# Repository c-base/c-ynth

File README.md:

c-ynth
======

data collection and source files for synth

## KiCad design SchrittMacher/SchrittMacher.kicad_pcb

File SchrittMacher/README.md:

# SchrittMacher

## Features

* 16 Step sequencer
* Gate Out
* Clock Out
* Clock In
* Global CV Out
* CV Out per Step
* Reset Per Step
* Reset In 

## Parts

* 2x 4017

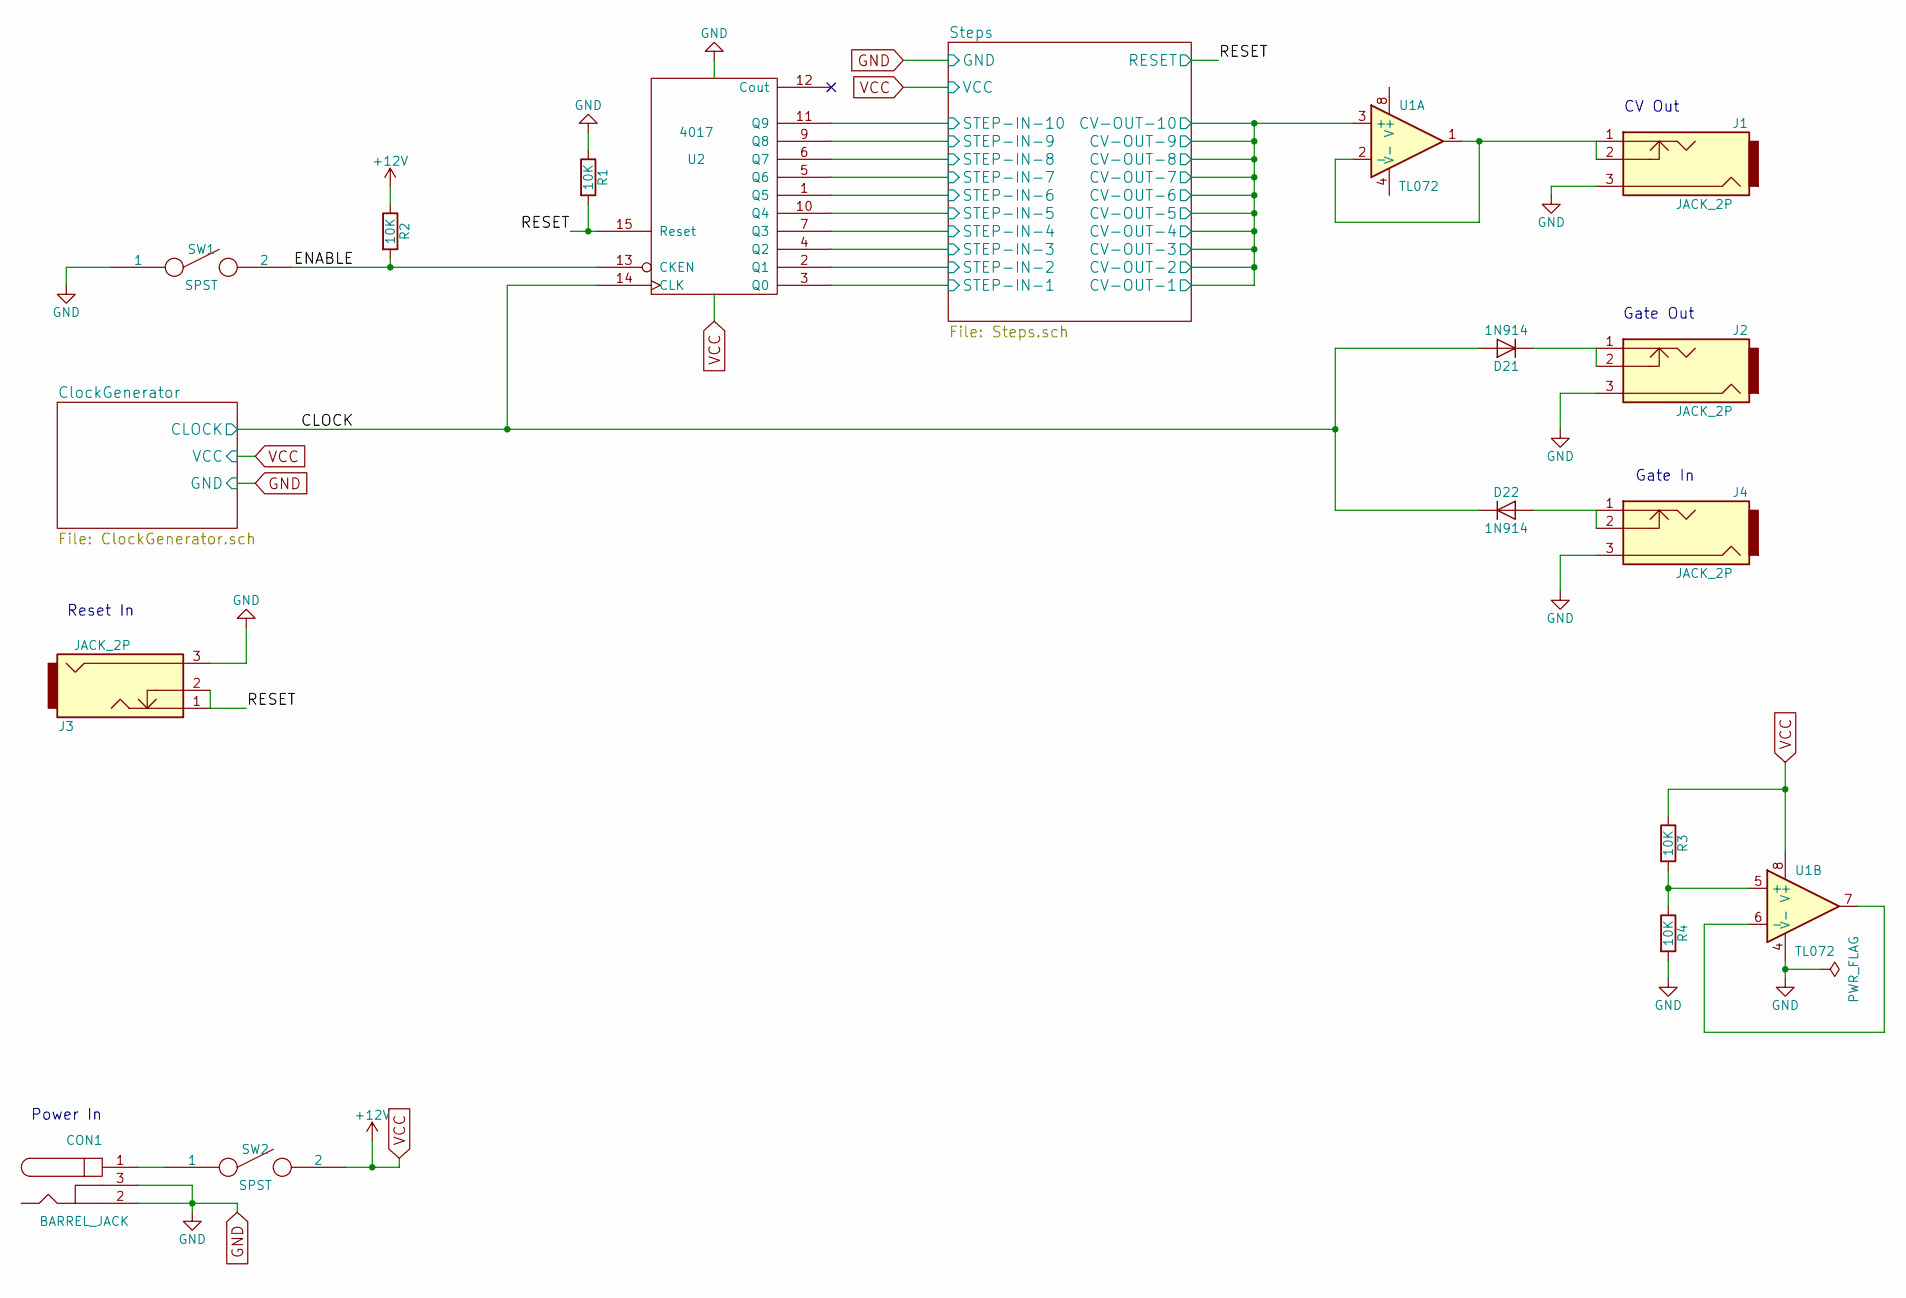
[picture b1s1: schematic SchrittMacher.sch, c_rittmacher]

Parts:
CON1: BARREL_JACK; JACK_ALIM
D21, D22: 1N914; Diode_DO-35_SOD27_Horizontal_RM10
J1, J2, J3, J4: JACK_2P; Socket_Strip_Straight_1x03
R1, R2, R3, R4: 10K; Resistor_Horizontal_RM10mm
SW1, SW2: SPST; Socket_Strip_Straight_1x02
U1: TL072; DIP-8_W7.62mm_LongPads
U2: 4017; DIP-16_W7.62mm_LongPads

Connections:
/CLOCK: D21.2 (A), D22.1 (K), U2.14 (CLK); also elsewhere on the board
/ENABLE: R2.2, SW1.2, U2.13 (CKEN)
/RESET: J3.1, J3.2, R1.2, U2.15 (Reset); also elsewhere on the board
/Steps/CV-OUT-1: U1.3 (+); also elsewhere on the board
/Steps/STEP-IN-1: U2.3 (Q0); also elsewhere on the board
/Steps/STEP-IN-2: U2.2 (Q1); also elsewhere on the board
/Steps/STEP-IN-3: U2.4 (Q2); also elsewhere on the board
/Steps/STEP-IN-4: U2.7 (Q3); also elsewhere on the board
/Steps/STEP-IN-5: U2.10 (Q4); also elsewhere on the board
/Steps/STEP-IN-6: U2.1 (Q5); also elsewhere on the board
/Steps/STEP-IN-7: U2.5 (Q6); also elsewhere on the board
/Steps/STEP-IN-8: U2.6 (Q7); also elsewhere on the board
/Steps/STEP-IN-9: U2.9 (Q8); also elsewhere on the board
/Steps/STEP-IN-10: U2.11 (Q9); also elsewhere on the board
GND: CON1.2, CON1.3, J1.3, J2.3, J3.3, J4.3, R1.1, R4.2, SW1.1, U1.4 (V-), U2.8 (VSS); also elsewhere on the board
unnamed: CON1.1, SW2.1
unnamed: D21.1 (K), J2.1, J2.2
unnamed: D22.2 (A), J4.1, J4.2
unnamed: J1.1, J1.2, U1.1, U1.2 (-)
unnamed: R3.2, R4.1, U1.5 (+)
unnamed: U1.6 (-), U1.7
VCC: R2.1, R3.1, SW2.2, U1.8 (V+), U2.16 (VDD); also elsewhere on the board

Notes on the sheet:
Gate Out
Reset In
Power In
CV Out
Gate In

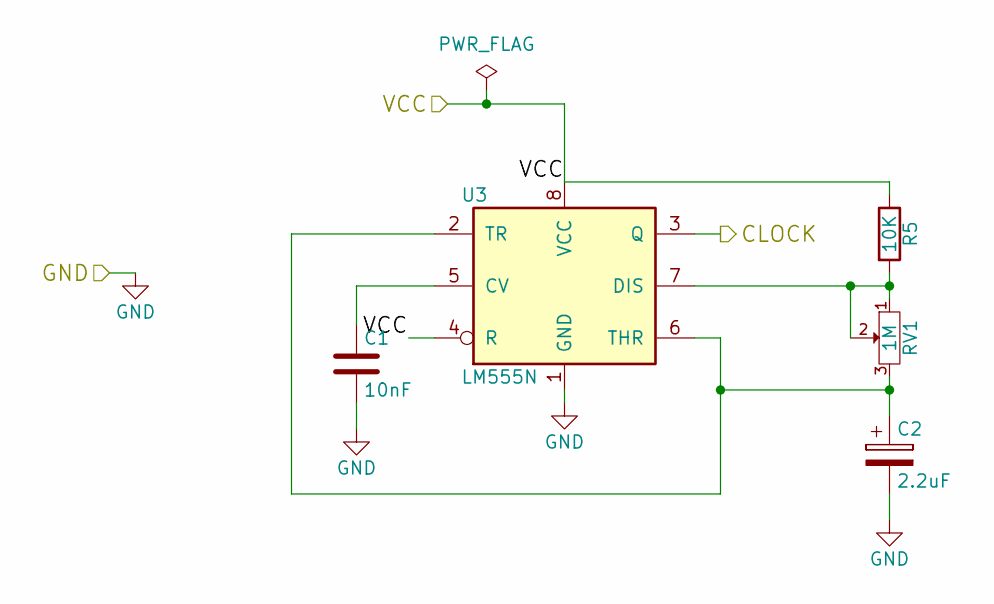
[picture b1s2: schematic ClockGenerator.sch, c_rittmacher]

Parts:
C1: 10nF; C_Disc_D3_P2.5
C2: 2.2uF; C_Radial_D5_L6_P2.5
R5: 10K; Resistor_Horizontal_RM10mm
RV1: 1M; Potentiometer_WirePads_Small
U3: LM555N; DIP-8_W7.62mm_LongPads

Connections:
/CLOCK: U3.3 (Q); also elsewhere on the board
GND: C1.2, C2.2, U3.1 (GND); also elsewhere on the board
unnamed: C1.1, U3.5 (CV)
unnamed: C2.1, RV1.3, U3.2 (TR), U3.6 (THR)
unnamed: R5.2, RV1.1, RV1.2, U3.7 (DIS)
VCC: R5.1, U3.4 (R), U3.8 (VCC); also elsewhere on the board

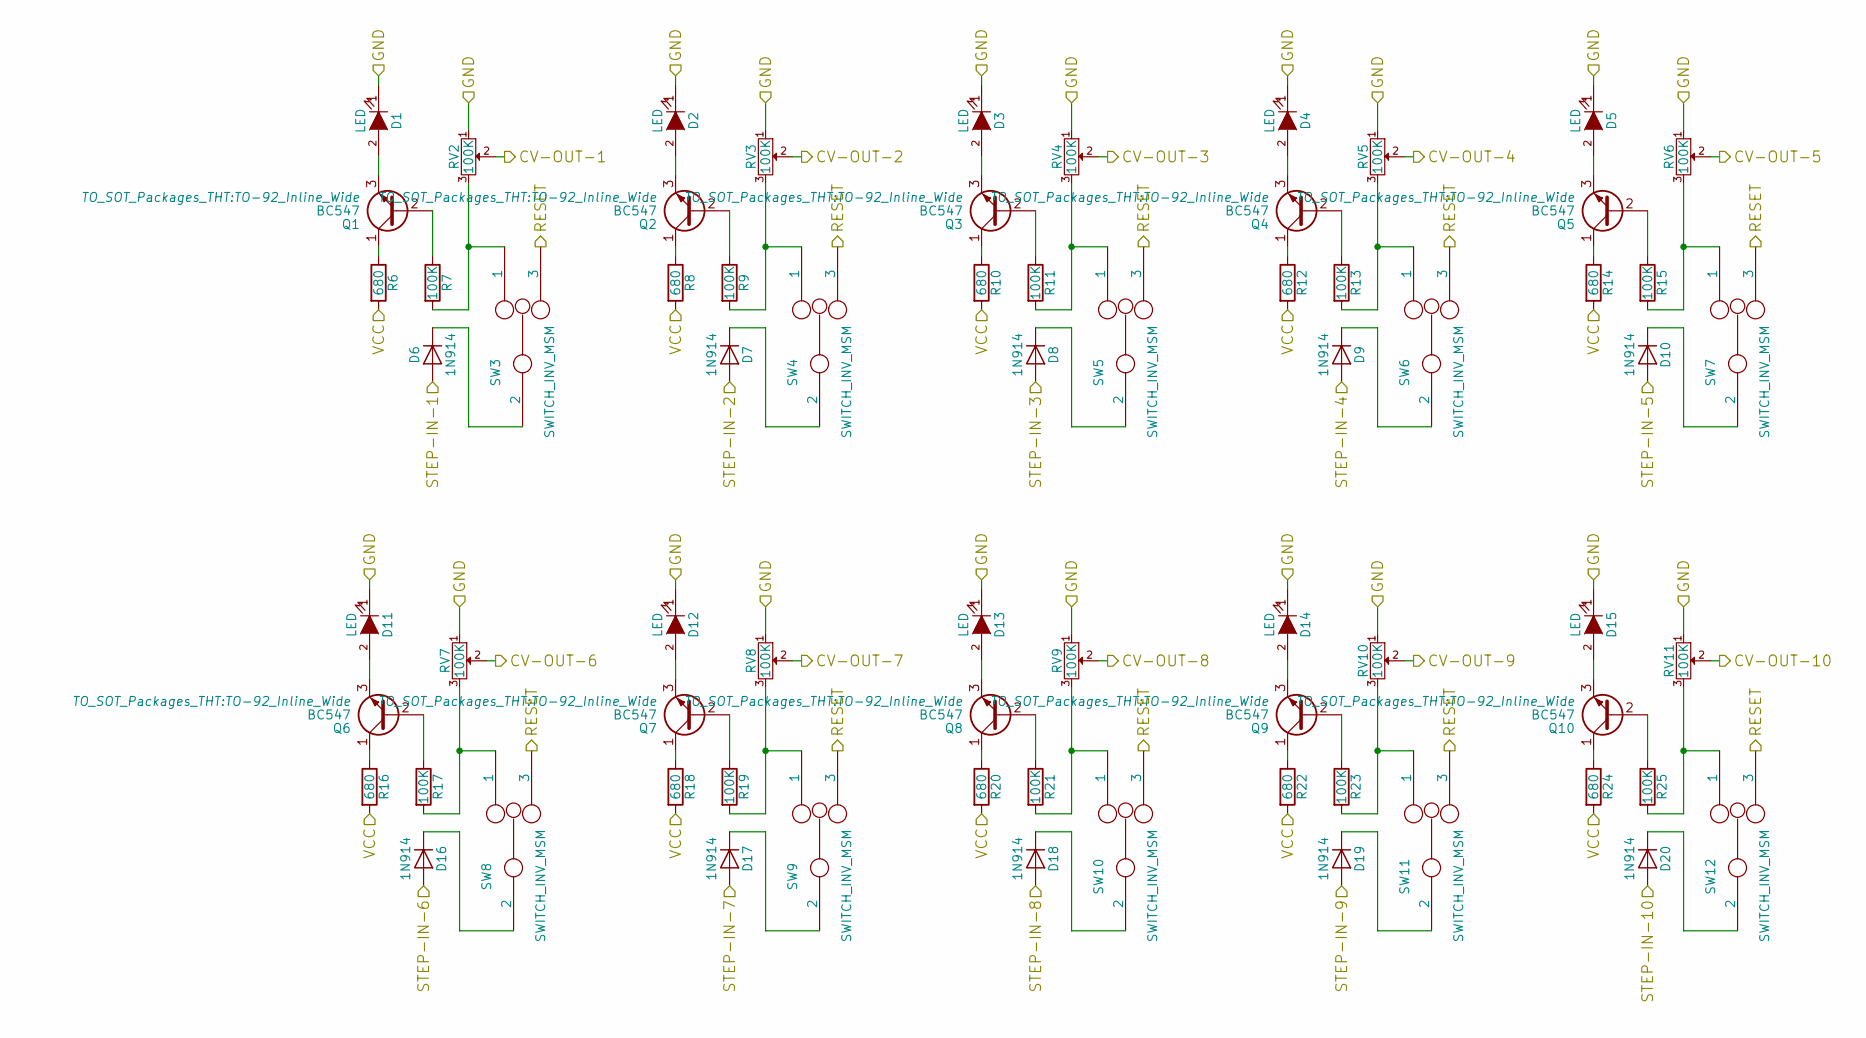
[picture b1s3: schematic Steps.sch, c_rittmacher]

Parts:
D1, D2, D3, D4, D5, D11, D12, D13, D14, D15: LED; LED-5MM
D6, D7, D8, D9, D10, D16, D17, D18, D19, D20: 1N914; Diode_DO-35_SOD27_Horizontal_RM10
Q1, Q2, Q3, Q4, Q5, Q6, Q7, Q8, Q9, Q10: BC547; TO-92_Inline_Wide
R6, R8, R10, R12, R14, R16, R18, R20, R22, R24: 680; Resistor_Horizontal_RM10mm
R7, R9, R11, R13, R15, R17, R19, R21, R23, R25: 100K; Resistor_Horizontal_RM10mm
RV2, RV3, RV4, RV5, RV6, RV7, RV8, RV9, RV10, RV11: 100K; Potentiometer_WirePads_Small
SW3, SW4, SW5, SW6, SW7, SW8, SW9, SW10, SW11, SW12: SWITCH_INV_MSM; SW_Micro_SPST

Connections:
/RESET: SW3.3, SW4.3, SW5.3, SW6.3, SW7.3, SW8.3, SW9.3, SW10.3, SW11.3, SW12.3; also elsewhere on the board
/Steps/CV-OUT-1: RV2.2, RV3.2, RV4.2, RV5.2, RV6.2, RV7.2, RV8.2, RV9.2, RV10.2, RV11.2; also elsewhere on the board
/Steps/STEP-IN-1: D6.2 (A); also elsewhere on the board
/Steps/STEP-IN-2: D7.2 (A); also elsewhere on the board
/Steps/STEP-IN-3: D8.2 (A); also elsewhere on the board
/Steps/STEP-IN-4: D9.2 (A); also elsewhere on the board
/Steps/STEP-IN-5: D10.2 (A); also elsewhere on the board
/Steps/STEP-IN-6: D16.2 (A); also elsewhere on the board
/Steps/STEP-IN-7: D17.2 (A); also elsewhere on the board
/Steps/STEP-IN-8: D18.2 (A); also elsewhere on the board
/Steps/STEP-IN-9: D19.2 (A); also elsewhere on the board
/Steps/STEP-IN-10: D20.2 (A); also elsewhere on the board
GND: D1.1 (K), D2.1 (K), D3.1 (K), D4.1 (K), D5.1 (K), D11.1 (K), D12.1 (K), D13.1 (K), D14.1 (K), D15.1 (K), RV2.1, RV3.1, RV4.1, RV5.1, RV6.1, RV7.1, RV8.1, RV9.1, RV10.1, RV11.1; also elsewhere on the board
unnamed: D1.2 (A), Q1.3 (E)
unnamed: D2.2 (A), Q2.3 (E)
unnamed: D3.2 (A), Q3.3 (E)
unnamed: D4.2 (A), Q4.3 (E)
unnamed: D5.2 (A), Q5.3 (E)
unnamed: D6.1 (K), SW3.2
unnamed: D7.1 (K), SW4.2
unnamed: D8.1 (K), SW5.2
unnamed: D9.1 (K), SW6.2
unnamed: D10.1 (K), SW7.2
unnamed: D11.2 (A), Q6.3 (E)
unnamed: D12.2 (A), Q7.3 (E)
unnamed: D13.2 (A), Q8.3 (E)
unnamed: D14.2 (A), Q9.3 (E)
unnamed: D15.2 (A), Q10.3 (E)
unnamed: D16.1 (K), SW8.2
unnamed: D17.1 (K), SW9.2
unnamed: D18.1 (K), SW10.2
unnamed: D19.1 (K), SW11.2
unnamed: D20.1 (K), SW12.2
unnamed: Q1.1 (C), R6.1
unnamed: Q1.2 (B), R7.1
unnamed: Q2.1 (C), R8.1
unnamed: Q2.2 (B), R9.1
unnamed: Q3.1 (C), R10.1
unnamed: Q3.2 (B), R11.1
unnamed: Q4.1 (C), R12.1
unnamed: Q4.2 (B), R13.1
unnamed: Q5.1 (C), R14.1
unnamed: Q5.2 (B), R15.1
unnamed: Q6.1 (C), R16.1
unnamed: Q6.2 (B), R17.1
unnamed: Q7.1 (C), R18.1
unnamed: Q7.2 (B), R19.1
unnamed: Q8.1 (C), R20.1
unnamed: Q8.2 (B), R21.1
unnamed: Q9.1 (C), R22.1
unnamed: Q9.2 (B), R23.1
unnamed: Q10.1 (C), R24.1
unnamed: Q10.2 (B), R25.1
unnamed: R7.2, RV2.3, SW3.1
unnamed: R9.2, RV3.3, SW4.1
unnamed: R11.2, RV4.3, SW5.1
unnamed: R13.2, RV5.3, SW6.1
unnamed: R15.2, RV6.3, SW7.1
unnamed: R17.2, RV7.3, SW8.1
unnamed: R19.2, RV8.3, SW9.1
unnamed: R21.2, RV9.3, SW10.1
unnamed: R23.2, RV10.3, SW11.1
unnamed: R25.2, RV11.3, SW12.1
VCC: R6.2, R8.2, R10.2, R12.2, R14.2, R16.2, R18.2, R20.2, R22.2, R24.2; also elsewhere on the board

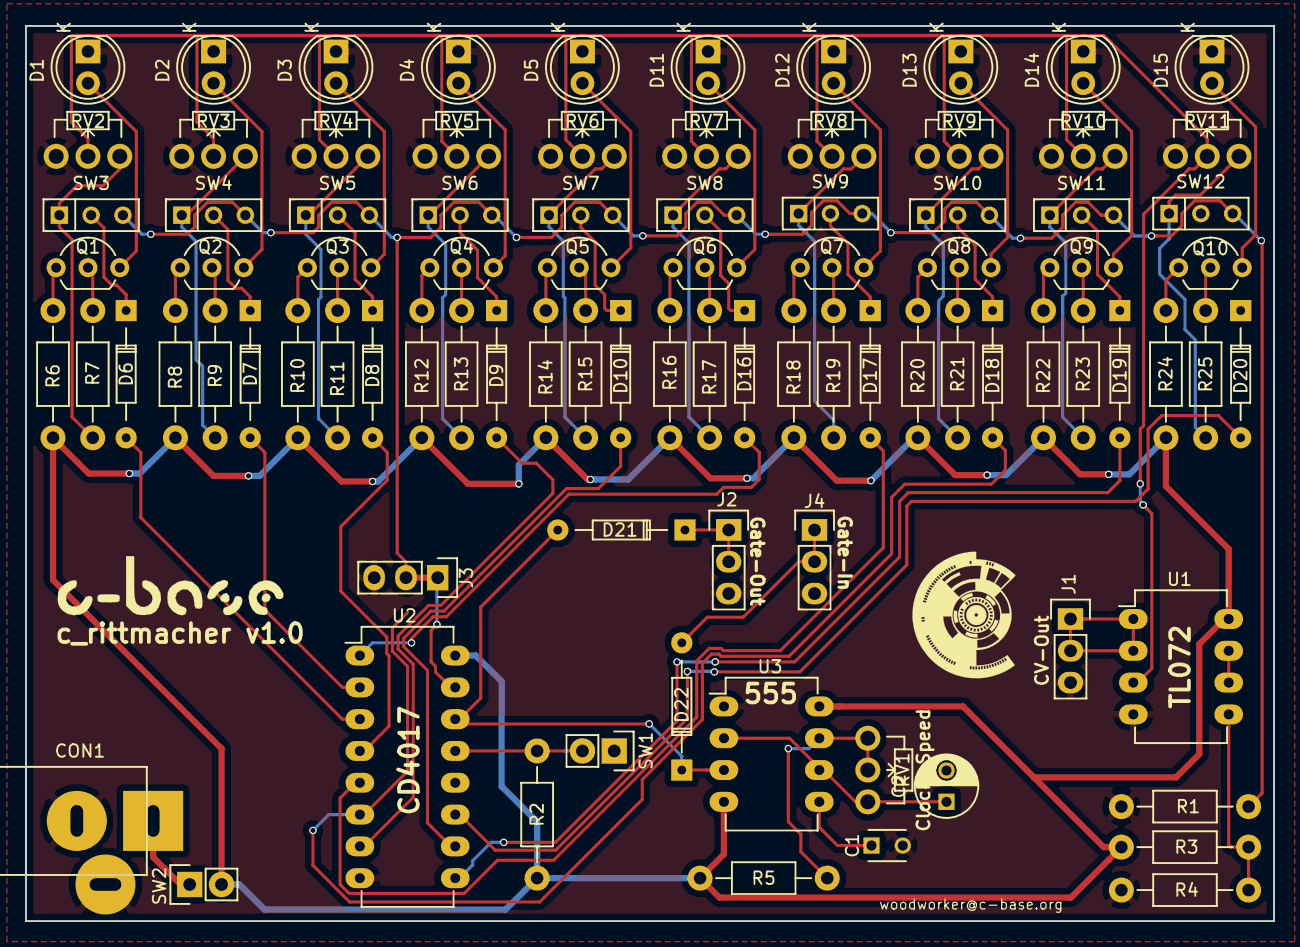
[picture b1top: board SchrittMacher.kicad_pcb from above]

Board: 2 copper layers, 99.7 x 71.5 mm, 90 parts (0 on the bottom side), 75 nets.

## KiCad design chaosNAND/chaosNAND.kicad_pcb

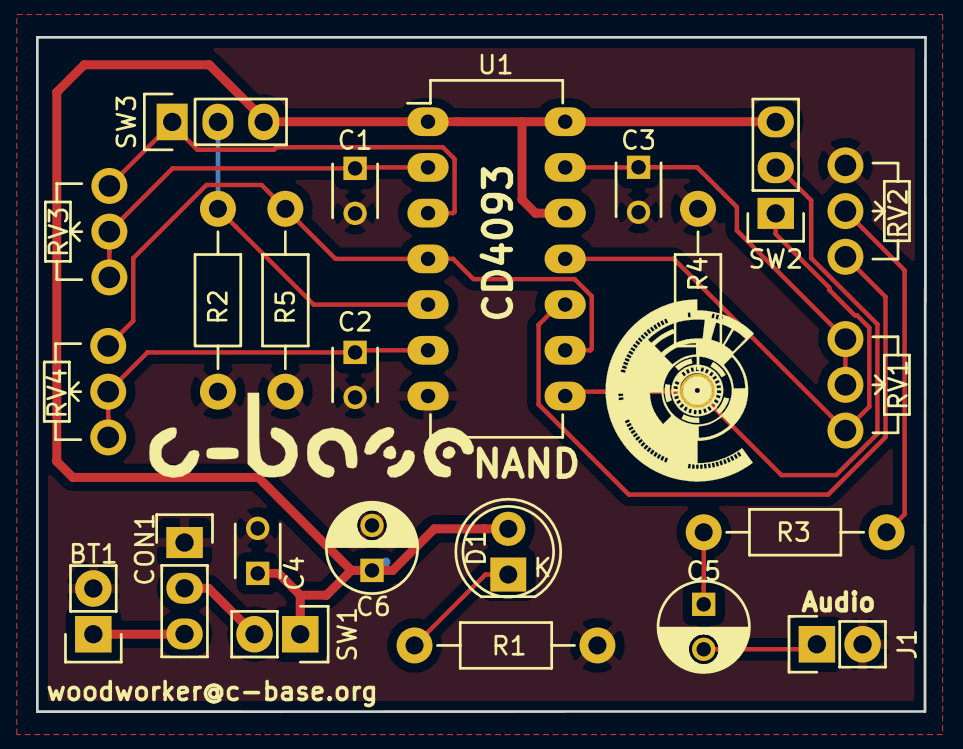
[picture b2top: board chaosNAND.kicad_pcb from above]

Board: 2 copper layers, 49.3 x 37.5 mm, 23 parts (0 on the bottom side), 17 nets.

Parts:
BT1: Battery; Pin_Header_Straight_1x02
C1, C2, C3, C4: 0.1uF; C_Disc_D3_P2.5
C5: 2.2uF; C_Radial_D5_L6_P2.5
C6: 100uF; C_Radial_D5_L6_P2.5
CON1: BARREL_JACK; Pin_Header_Straight_1x03
D1: LED; LED-5MM
J1: JACK_MONO; Pin_Header_Straight_1x02
R1: 1K; Resistor_Horizontal_RM10mm
R2, R3, R4, R5: 100K; Resistor_Horizontal_RM10mm
RV1, RV3: 1M; Potentiometer_WirePads_Small
RV2: 100KA; Potentiometer_WirePads_Small
RV4: 100K; Potentiometer_WirePads_Small
SW1: SPST; Pin_Header_Straight_1x02
SW2, SW3: SWITCH_INV; Pin_Header_Straight_1x03
U1: 4093; DIP-14_W7.62mm_LongPads

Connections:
+9V: C4.1, C6.1, D1.2, SW1.1, SW2.3, SW3.3, U1.1, U1.12, U1.14
GND: BT1.2, C1.2, C2.2, C3.2, C4.2, C6.2, CON1.1, J1.2, R1.2, R2.2, R4.2, R5.2, RV2.1, U1.7
unnamed: BT1.1, CON1.3
unnamed: C1.1, RV3.1, RV3.2, U1.2
unnamed: C2.1, RV4.1, RV4.2, U1.6
unnamed: C3.1, RV1.1, RV1.2, U1.13
unnamed: C5.1, R3.1
unnamed: C5.2, J1.1
unnamed: CON1.2, SW1.2
unnamed: D1.1, R1.1
unnamed: R2.1, SW3.2, U1.5
unnamed: R3.2, RV2.2
unnamed: R4.1, SW2.2, U1.8
unnamed: R5.1, RV4.3, U1.4, U1.9
unnamed: RV1.3, SW2.1, U1.11
unnamed: RV2.3, U1.10
unnamed: RV3.3, SW3.1, U1.3

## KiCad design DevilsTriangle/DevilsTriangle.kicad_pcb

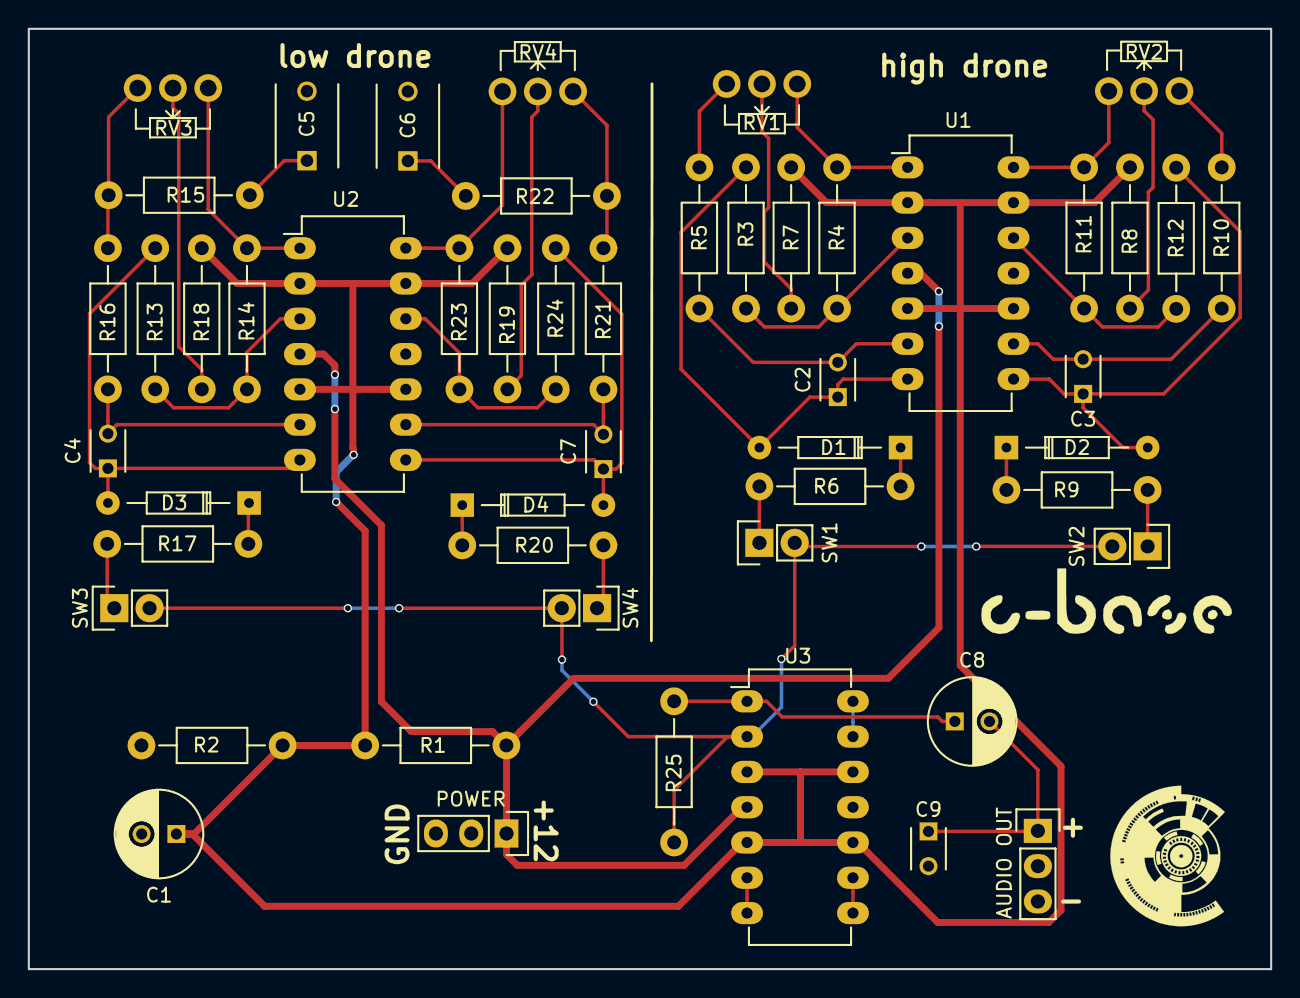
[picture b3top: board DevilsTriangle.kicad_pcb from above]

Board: 2 copper layers, 89.4 x 67.7 mm, 51 parts (0 on the bottom side), 43 nets.

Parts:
AUDIO OUT: JACK_2P; Pin_Header_Straight_1x03
C1, C8: 100uF; C_Radial_D6.3_L11.2_P2.5
C2, C3, C4, C7: 4.7nF; C_Disc_D3_P2.5
C5, C6: 470nF; C_Disc_D6_P5
C9: 1nF; C_Disc_D3_P2.5
D1, D2, D3, D4: 1N914; Diode_DO-35_SOD27_Horizontal_RM10
POWER: BARREL_JACK; Pin_Header_Straight_1x03
R1, R2, R7, R8, R18, R19: 10K; Resistor_Horizontal_RM10mm
R3, R12, R13, R24: 33K; Resistor_Horizontal_RM10mm
R4, R11, R14, R23: 47K; Resistor_Horizontal_RM10mm
R5, R10, R16, R21: 220K; Resistor_Horizontal_RM10mm
R6, R9, R15, R22, R25: 100K; Resistor_Horizontal_RM10mm
R17, R20: R; Resistor_Horizontal_RM10mm
RV1, RV2, RV3, RV4: 100K; Potentiometer_WirePads_Small
SW1, SW2, SW3, SW4: SPST; Pin_Header_Straight_1x02
U1, U2, U3: LM324N; DIP-14_W7.62mm_LongPads

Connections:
+12V: POWER.1, R1.1, U1.4, U2.4, U3.4
/Buffer/MIX-OUT: AUDIO OUT.1, C8.2, C9.1
/Buffer/VOICE-IN: R25.2, SW1.2, SW2.2, SW3.2, SW4.2, U3.2
/Buffer/VREF: C1.1, R1.2, R2.1, R7.2, R8.1, R18.2, R19.1, U1.2, U1.5, U1.10, U1.13, U2.2, U2.5, U2.10, U2.13, U3.3, U3.5, U3.10, U3.12
GND: AUDIO OUT.3, C1.2, C5.2, C6.2, C9.2, POWER.2, POWER.3, R2.2, U1.11, U2.11, U3.11
unnamed: C2.1, D1.2, R3.1, U1.7
unnamed: C2.2, R5.1, U1.6
unnamed: C3.1, D2.2, R12.1, U1.8
unnamed: C3.2, R10.1, U1.9
unnamed: C4.1, D3.2, R13.1, U2.7
unnamed: C4.2, R16.1, U2.6
unnamed: C5.1, R15.2
unnamed: C6.1, R22.2
unnamed: C7.1, D4.2, R24.1, U2.8
unnamed: C7.2, R21.1, U2.9
unnamed: C8.1, R25.1, U3.1
unnamed: D1.1, R6.2
unnamed: D2.1, R9.2
unnamed: D3.1, R17.2
unnamed: D4.1, R20.2
unnamed: R3.2, R4.2, U1.3
unnamed: R4.1, RV1.1, U1.1
unnamed: R5.2, RV1.3
unnamed: R6.1, SW1.1
unnamed: R7.1, RV1.2
unnamed: R8.2, RV2.2
unnamed: R9.1, SW2.1
unnamed: R10.2, RV2.3
unnamed: R11.1, RV2.1, U1.14
unnamed: R11.2, R12.2, U1.12
unnamed: R13.2, R14.2, U2.3
unnamed: R14.1, RV3.1, U2.1
unnamed: R15.1, R16.2, RV3.3
unnamed: R17.1, SW3.1
unnamed: R18.1, RV3.2
unnamed: R19.2, RV4.2
unnamed: R20.1, SW4.1
unnamed: R21.2, R22.1, RV4.3
unnamed: R23.1, RV4.1, U2.14
unnamed: R23.2, R24.2, U2.12
unnamed: U3.6, U3.7
unnamed: U3.8, U3.9
unnamed: U3.13, U3.14

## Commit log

2013-12-03 added 40106 Oscillator
2013-12-10 Added Sinusgeneratoren
2013-12-10 added ICL8038
2013-12-11 added yusynth
2013-12-30 added some step sequencer links
2014-06-06 added aftertouch velocity howto
2014-06-23 added 4066 ic
2014-08-04 added pt2399 description
2015-08-20 added 4093
2015-08-25 added Circuitsnippets
2015-09-01 added Paul In The Lab
2015-09-07 added Design Your Own Distortion
2015-09-15 Devils Triangle Synth - LowDrone Schematic and Board
2016-01-28 Added OPA2134, UAF42, DRV134PA, and INA134PA
2016-01-29 added MSGEQ7
2016-03-17 added NJM2073
2016-03-21 added SchrittMacher projekt
2016-03-25 redone the devils triangle in kicad
2016-03-26 added chaosNAND project
2016-03-26 made lib path relative
2016-03-27 added c-base markings to the PCB
2016-03-28 more silkscreen
2016-04-03 added LT1054 Switched-Capacitor Voltage Converter
2018-01-14 fixed some circuit problems in schrittmacher
2018-05-26 added 4089
2018-06-01 added some links
